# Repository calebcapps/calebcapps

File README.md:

- 👋 Hi, I’m @calebcapps
- 👀 I’m interested in Solidworks API, Python, Arduino, and GUI design!
- 🌱 I’m currently learning Python, C#, .NET, and VBA
- 📫 How to reach me caleb.capps@jrautomation.com

<!---
calebcapps/calebcapps is a ✨ special ✨ repository because its `README.md` (this file) appears on your GitHub profile.
You can click the Preview link to take a look at your changes.
--->

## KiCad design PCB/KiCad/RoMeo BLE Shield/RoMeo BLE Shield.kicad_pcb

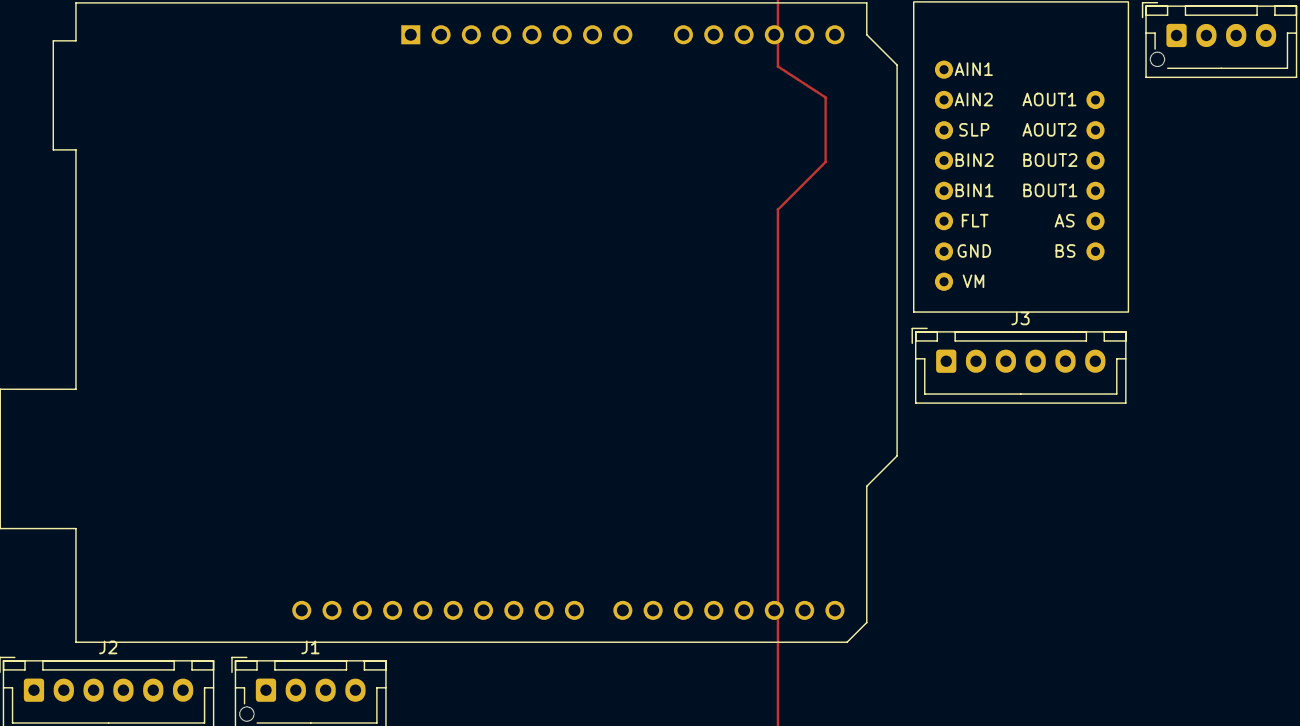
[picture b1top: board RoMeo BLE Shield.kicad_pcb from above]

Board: 2 copper layers, 6 parts (0 on the bottom side), 2 nets, no tracks yet.

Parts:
A1: Arduino_UNO_R3
J1, J4: Conn_01x04; JST_XH_B4B-XH-AM_1x04_P2.50mm_Vertical
J2, J3: Conn_01x06; JST_XH_B6B-XH-A_1x06_P2.50mm_Vertical
U1: DRV8833 Breakout

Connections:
D9: A1.24 (D9), J4.1
Earth: A1.7 (GND), J4.3

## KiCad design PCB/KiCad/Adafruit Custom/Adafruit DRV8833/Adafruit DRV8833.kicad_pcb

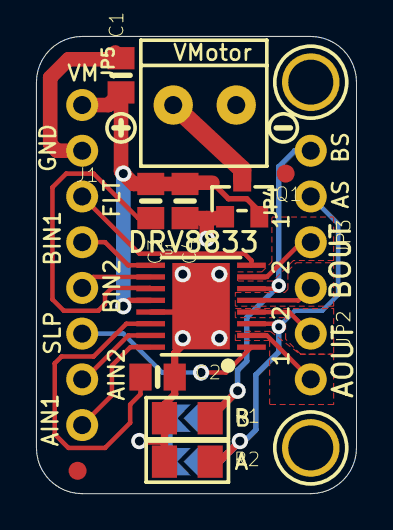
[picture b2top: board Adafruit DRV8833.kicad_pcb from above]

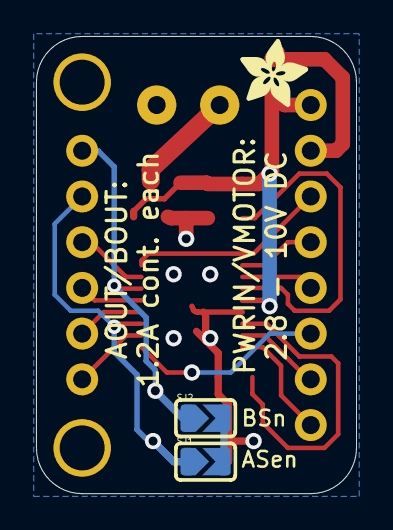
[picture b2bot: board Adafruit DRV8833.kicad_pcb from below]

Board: 2 copper layers, 17.8 x 25.4 mm, 22 parts (3 on the bottom side), 17 nets.

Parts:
C1, C4: 10µF/16V; 0805-NO
C2: 10µF; 0805-NO
C3: 0.1uF; 0805-NO
FID1, FID2: FIDUCIAL""; FIDUCIAL_1MM
J1: VMOTORIN; TERMBLOCK_1X2-3.5MM
JP2, JP3, JP4: HEADER-1X2ROUND; 1X02_ROUND
JP5: HEADER-1X870MIL; 1X08_ROUND_70
Q1: DMG3415U; SOT23-WIDE
R1, R2: 0.2Ω; _1206
SJ1: ISENSEA; SOLDERJUMPER_ARROW_NOPASTE
SJ2: ISENSEB; SOLDERJUMPER_ARROW_NOPASTE
U1: DRV8833PWPR; HTSSOP16
U$13, U$14: MOUNTINGHOLE2.5; MOUNTINGHOLE_2.5_PLATED
U$15: SYMBOL_PLUS
U$16: SYMBOL_MINUS
U$17: ADAFRUIT_3.5MM

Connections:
/AIN1: JP5.8, U1.16 (A_IN1)
/AIN2: JP5.7, U1.15 (A_IN2)
/ASEN: JP4.1, R2.2, SJ1.1, U1.3 (A_ISENSE)
/BIN1: JP5.4, U1.9 (B_IN1)
/BIN2: JP5.5, U1.10 (B_IN2)
/BSEN: JP4.2, R1.2, SJ2.1, U1.6 (B_ISENSE)
/NFAULT: JP5.3, U1.8 (NFAULT)
/VINT: C2.1, U1.14 (VINT)
/~SLEEP: JP5.6, U1.1 (NSLEEP)
GND: C1.2, C2.2, C4.2, J1.2, JP5.2, Q1.1 (G), R1.1, R2.1, SJ1.2, SJ2.2, U1.13 (GND@1), U1.PPAD (GND(THRML))
unnamed: C3.2, U1.11 (VCP)
unnamed: J1.1, Q1.3 (D)
unnamed: JP2.1, U1.4 (A_OUT2)
unnamed: JP2.2, U1.2 (A_OUT1)
unnamed: JP3.1, U1.7 (B_OUT1)
unnamed: JP3.2, U1.5 (B_OUT2)
VMOTOR: C1.1, C3.1, C4.1, JP5.1, Q1.2 (S), U1.12 (VM)

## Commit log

2022-05-23 added libraries
2022-05-27 added speech recongnition module
2022-06-07 Python Dash Tutorial Examples
2022-06-30 added 3DP recipe form template
    still needs backend logic
2022-07-15 3DP recipe update
2022-08-02 added sample python code for pyfirmata
2022-08-02 Added arduino firmata servo example sketch
2022-08-30 Python Dash examples
2023-01-18 update python with telemetrix project skeleton
2023-02-02 added ESP32 blink hello world and XML layout for ESP32 (WIP)
2023-02-02 added blink hello world foe esp32 and removed telemetrix
2023-02-10 adding ESP32 soft AP IP communication example to PC over websocket
2023-02-16 added get_addresses method
    added a get_addresses method to enable syncing the hex address tags between the ESP32 and the python programs
2023-02-24 added ESP32 python two-way interface for digital read and write
2023-02-28 added support for SERVO commands, cleaned up definitions location
2023-02-28 added servo webpage interaction script
2023-02-28 littlFS example files
2023-04-04 Added in webpage rendering call for .STL files
2023-04-06 added helper.py module for clean up main, removed redundant information
2023-04-12 Dir changed
2025-11-17 Add files via upload
    Deck TeleOp combines both Python and Arduino code that will be ran on a Steam Deck and WiFi-Enabled microcontroller (e.g. ESP-32) to allow the Steam deck to act as a teleoperator controller
